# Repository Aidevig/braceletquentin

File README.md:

# braceletquentin
Schémas, code et documentation du bracelet développé par Quentin

#	Code
Code pour Adafruit feather bluefruit m0

# Schemas
Fichier eagles, BOM et archives avec gerber pour fabrication de la carte

# Utilitaire USB
Tentative de programme récupérant les données stockées sur le bracelet directement en USB.
Echec : trop lent.

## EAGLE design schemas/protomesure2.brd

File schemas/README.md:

# Schema Electronique

Le fichier schema electronique est un fichier Eagle. Il contient le schéma électronique complet du prototype. Pour le réaliser, j'ai utilisé les schémas mis à disposition par adafruit sur ses différents modules. Ils sont aisément trouvables.

# Composants :
Microcontrolleur: 
Adafruit Feather M0 Bluefruit LE	https://www.adafruit.com/product/2995

Accéléromètre:
ADXL345 							https://www.adafruit.com/product/1231

Capteur Cardiaque:
BH1790GLC							http://www.rohm.com/web/global/products/-/product/BH1790GLC

micro:
Electret Microphone Amplifier - MAX4466 with Adjustable gain	https://www.adafruit.com/product/1063

# PCB
Le répertoire PCB contient le .brd (format eagle). Il contient également les gerbers et la BOM.

# Commander un PCB
Afin de commander un pcb assemblé il suffit d'utiliser les fichiers contenus dans l'archive PCB-BODYGUARD.rar et la BOM car les composants sont déjà correspondants entre la BOM et le .brd

Passer par le site EMSPROTO et compter deux semaines pour des prix corrects.
	
# A faire
-La carte électronique est conçue sans bouton bien que les trous soient présent pour venir en souder deux. Il faut également ajouter un vibreur sur le pin A0.
Ceci permet d'ajouter ces périphériques directement sur la structure mécanique de l'objet.
-La carte électronique vient également sans son microcontrôleur feather M0 Bluefruit qui doit être soudé dessus. Il est immaginable d'ajouter un connecteur à la place afin d'éviter d'avoir à souder le microcontrôleur.
-La batterie utilisée est une batterie adafruit compatible avec le Feather M0 Bluefruit LE, elle se recharge lorsque le bracelet est branché en USB. Le bracelet doit être allumé pour se recharger.
-Un fil de la batterie doit être coupé et soudé a un switch intégré à la structure mécanique afin de pouvoir allumer et éteindre le bracelet 	
	
# ATTENTION
Afin d'optimiser l'espace sur la carte, j'ai supprimé les boutons poussoirs. Il ne reste que le trou pour les connecter aux pins du microcontrôleur. Il faudra également connecter l'autre entrée à la masse.
Par conséquent, les fichiers eagles du schéma et de la board ne sont plus linkés. AUCUNE MODIFICATION SUR L'UN N'AURA D'EFFET SUR L'AUTRE

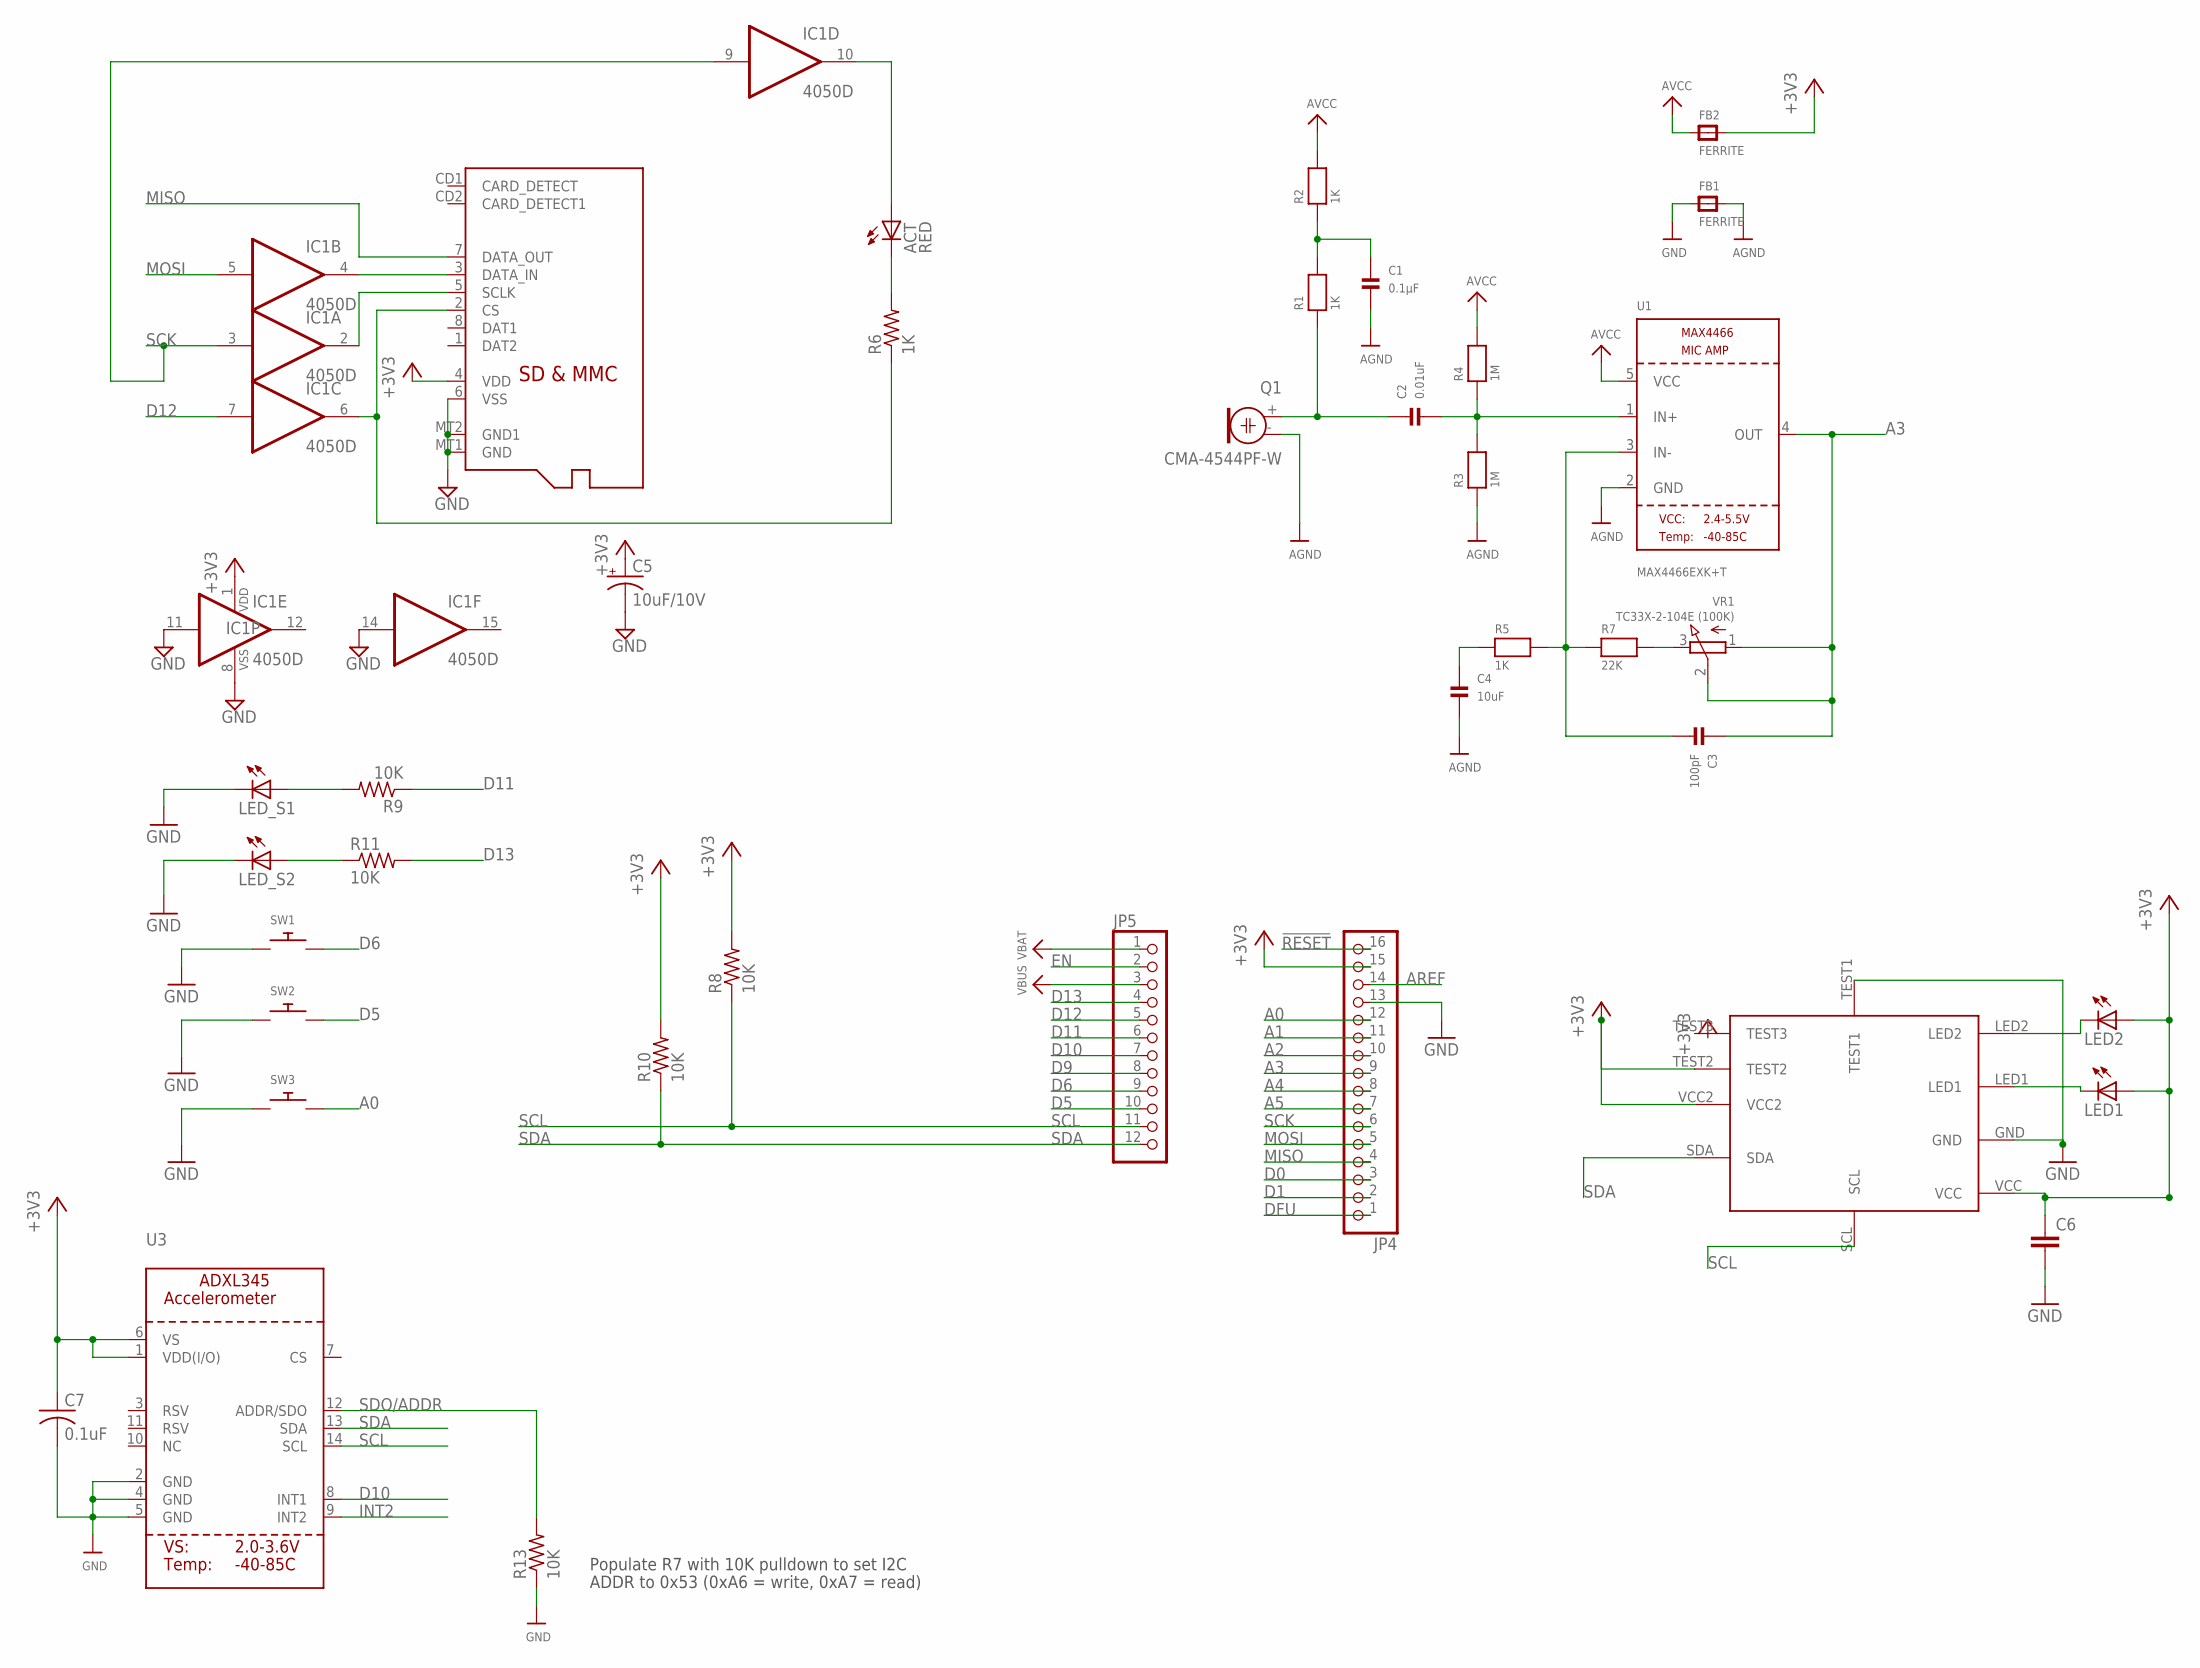
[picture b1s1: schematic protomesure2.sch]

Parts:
ACT: RED; CHIP-LED0805
C1: 0.1µF; 0805
C2: 0.01uF; 0805
C3: 100pF; 0805
C4: 10uF; 0805
C5: 10uF/10V; A/3216-18R
C6: C-EUC0805; C0805
C7: 0.1uF; C0805
FB1, FB2: FERRITE; 0805
IC1: 4050D; SO16
JP4: HEADER-1X16ROUND; 1X16_ROUND
JP5: HEADER-1X12; 1X12_ROUND
LED1, LED2: LEDCHIPLED_0805; CHIPLED_0805
LED_S1, LED_S2: LEDCHIPLED_0805; CHIPLED_0805
Q1: CMA-4544PF-W; ELECTRET_9.7
R1, R2, R5: 1K; 0805
R3, R4: 1M; 0805
R6: 1K; R0805
R7: 22K; 0805
R8, R9, R10, R11, R13: 10K; R0805
SW1, SW2, SW3: SWITCH_PUSHBUTTONEVQ-PE; TACT_PANA-EVQ
U1: MAX4466EXK+T; SC70-5
U3: ACCEL_ADXL345; LGA14
U$31: BH1790
VR1: TC33X-2-104E (100K); TRIMPOT_BOURNS_TC33X-2
X1: MICROSD

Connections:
!RESET: JP4.16
+3V3: C5.+, C6.1, C7.1, FB2.2, IC1.1 (VDD), JP4.15, LED1.A, LED2.A, R8.2, R10.2, U3.1 (VDD(I/O)), U3.6 (VS), U$31.TEST2, U$31.VCC, U$31.VCC2, X1.4 (VDD)
A0: JP4.12, SW3.P$2
A1: JP4.11
A2: JP4.10
A3: C3.1, JP4.9, U1.4 (OUT), VR1.1 (A), VR1.2 (S)
A4: JP4.8
A5: JP4.7
AGND: C1.2, C4.2, FB1.2, Q1.- (1), R3.1, U1.2 (GND)
AREF: JP4.14
AVCC: FB2.1, R2.2, R4.2, U1.5 (VCC)
D0: JP4.3
D1: JP4.2
D5: JP5.10, SW2.P$2
D6: JP5.9, SW1.P$2
D9: JP5.8
D10: JP5.7, U3.8 (INT1)
D11: JP5.6, R9.1
D12: IC1.7 (I), JP5.5
D13: JP5.4, R11.2
DFU: JP4.1
EN: JP5.2
GND: C5.-, C6.2, C7.2, FB1.1, IC1.8 (VSS), IC1.11 (I), IC1.14 (I), JP4.13, LED_S1.C, LED_S2.C, R13.1, SW1.P$1, SW2.P$1, SW3.P$1, U3.2 (GND), U3.4 (GND), U3.5 (GND), U$31.GND, U$31.TEST1, X1.6 (VSS), X1.MT1 (GND), X1.MT2 (GND1)
INT2: U3.9 (INT2)
MISO: JP4.4, X1.7 (DATA_OUT)
MOSI: IC1.5 (I), JP4.5
unnamed: C3.2, R5.2, R7.1, U1.3 (IN-)
unnamed: R7.2, VR1.3 (E)
unnamed: C2.1, Q1.+ (2), R1.1
unnamed: C1.1, R1.2, R2.1
unnamed: C2.2, R3.2, R4.1, U1.1 (IN+)
unnamed: LED1.C, U$31.LED1
unnamed: C4.1, R5.1
unnamed: ACT.A, IC1.10 (O)
unnamed: IC1.2 (O), X1.5 (SCLK)
unnamed: IC1.6 (O), R6.1, X1.2 (CS)
unnamed: ACT.C, R6.2
unnamed: IC1.4 (O), X1.3 (DATA_IN)
unnamed: LED2.C, U$31.LED2
unnamed: LED_S1.A, R9.2
unnamed: LED_S2.A, R11.1
SCK: IC1.3 (I), IC1.9 (I), JP4.6
SCL: JP5.11, R8.1, U3.14 (SCL), U$31.SCL
SDA: JP5.12, R10.1, U3.13 (SDA), U$31.SDA
SDO/ADDR: R13.2, U3.12 (ADDR/SDO)
VBAT: JP5.1
VBUS: JP5.3

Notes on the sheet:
Populate R7 with 10K pulldown to set I2C
ADDR to 0x53 (0xA6 = write, 0xA7 = read)

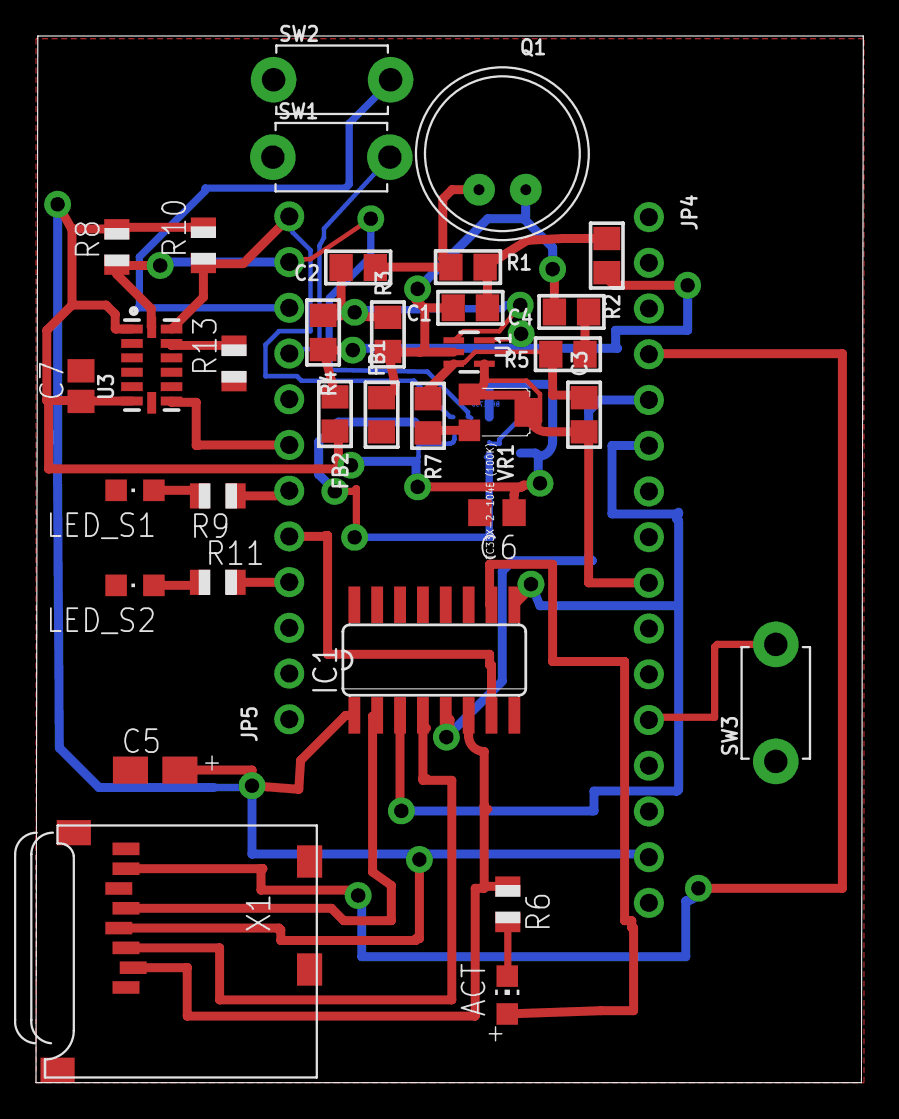
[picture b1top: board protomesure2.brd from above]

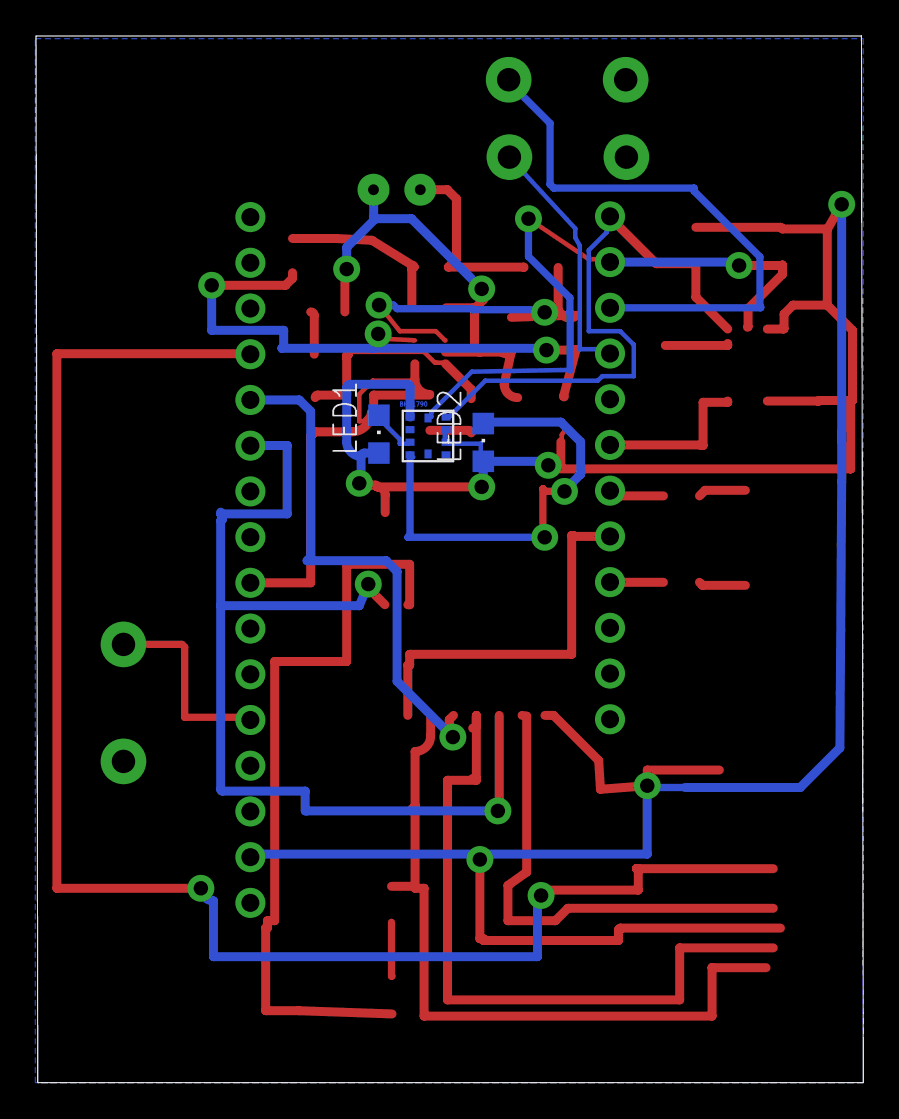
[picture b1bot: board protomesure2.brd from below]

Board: 2 copper layers, 46.0 x 58.1 mm, 38 parts (3 on the bottom side), 33 nets.

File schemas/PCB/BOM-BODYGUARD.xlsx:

Désignation | Quantity | Manufacturer | Reference Manufacturer | Supplier | Reference Supplier | MOUNTING TECHNOLOGY | Designator
Optical Sensor For Heart Rate Monitor | 1 | ROHM SEMICONDUCTOR | BH1790GLC-E2 | DIGIKEY | BH1790GLC-E2CT-ND | SMD | BH1790
LED BLUE-GREEN CLEAR 0603 SMD | 2 | ROHM SEMICONDUCTOR | SMLE13EC8TT86 | DIGIKEY | 846-1178-1-ND | SMD | LED1, LED2
LED green 0805 CMS | 1 | DIALIGHT | 5988270107F | FARNELL | 1850749 | SMD | LED5
LED RED 0805 CMS | 2 | DIALIGHT | 5988210107F | FARNELL | 1850747 | SMD | LED3, LED4
ADXL345BCCZ ACCELEROMETRE 3 AXES | 1 | ANALOG DEVICES | ADXL345BCCZ | FARNELL | 1853935 | SMD | ADXL
Buffer, Non-Inverseur | 1 | TEXAS INSTRUMENTS | CD74HC4050M | FARNELL | 1643824 | SMD | IC1
Connecteur carte SD | 1 | Adafruit | 1660 | MOUSER | 485-1660 | SMD | X1
Condensateur céramique multicouche CMS 100pF | 1 | MULTICOMP | MC0805N101J500CT | FARNELL | 1759203 | SMD | C3
Condensateur céramique multicouche CMS 0,01uF | 1 | MULTICOMP | MC0805F103Z500CT | FARNELL | 2665973 | SMD | C2
Condensateur céramique multicouche CMS 0,1uF | 2 | AVX | 08055C104KAT2A | FARNELL | 499687 | SMD | C1, C7
Condensateur céramique multicouche CMS 1uF | 1 | WALSIN | 0805B105K160CT | FARNELL | 2496946 | SMD | C6
Condensateur céramique multicouche CMS 10uF | 2 | WALSIN | 0805F106Z100CT | FARNELL | 2496998 | SMD | C4, C5
Resistance CMS 1K | 6 | MULTICOMP | MCHP05W4F1001T5E | FARNELL | 1576459 | SMD | R1, R2, R5, R6, R9, R11
Resistance CMS 10K | 3 | MULTICOMP | MCHP05W4F1002T5E | FARNELL | 1576473 | SMD | R8, R10, R13
Resistance CMS 22K | 1 | Welwyn | WCR0805-22KFI | FARNELL | 1099809 | SMD | R7
Resistance CMS 1M | 2 | MULTICOMP | MCHP05W4F1004T5E | FARNELL | 1576507 | SMD | R3, R4
Ferrite Beads 100MHz 600Ohm | 2 | WURTH ELEKTRONIK | 742792040 | MOUSER | 710-742792040 | SMD | FB1, FB2
Microphone | 1 | CUI INC | CMA-4544PF-W | DIGIKEY | 490-CMA-4544PF-W | Trans | Q1

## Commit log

2017-08-31 ajout readme
2017-08-31 Test
    Premier test d'ajout de fichier
2017-08-31 file test
    essais d'upload de file pour voir l'effet sur mon répertoire local
2017-08-31 test suppr
    Suppression du fichier ajouté lors du dernier commit. Celui-ci était
    bien apparu dans mon répertoire local.
2017-08-31 Revert "test suppr"
    This reverts commit 26754d58299ff16a1646c225599d6866bde89159.
2017-08-31 Fin des test
    Après test du revert, push pull, Suppression des fichiers inutiles pour
    la suite. Prêt à démarrer.
2017-08-31 Schemas du proto mesure
    Mise en vrac des différents fichiers.
2017-08-31 Code du bracelet
    Code très sale, à nettoyer, tester en situation et surtout MODULARISER.
    A faire en priorité
2017-10-02 design final du pcb
2017-10-16 En vue de la Review
    Code mis au propre
    + ajout des différents codes boutons et débounce
    + ajout d'une pseudo Rtc
2017-10-17 ajout des fichiers PCB
2017-10-17 Ajout des licenses et explication des librairies
2017-10-17 Déplacement de l'archive pcb-bdyguar.rar
2017-10-17 README electronique
2017-10-17 rectif readme Elec
2017-10-17 corrections readme elec
2017-10-17 Ajout de la license
2017-10-17 ajout de la license aidevig
2017-10-17 Correctif envois des données
2017-10-18 Utilitaire USB + alerte autocardio + seuils from SD
2017-10-18 readme general
2017-10-18 readme code
2017-10-18 readme
2017-10-18 localisation du #define DEBUG
2017-11-02 suppression gestion des interruptions car bug avec Accéléromètre

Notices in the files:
parts and their libraries:
microbuilder: This work is placed in the public domain, and may be freely used for commercial and non-commercial work with the following conditions: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
